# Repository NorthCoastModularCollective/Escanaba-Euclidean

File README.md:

# EuclideanTrigger
A simple module, based on the ATtiny85 that creates euclidean beats from a clock input. [under development]

The Escanaba Euclidean module has 3 alternate firmware modes:
## Escanaba Euclidean Firmware 
The Eucliean firmware generates euclidean rhythms synchronized to an external eurorack clock source. If no clock source is available it will self clock. Its 3 controls are as follows: 
- Number of hits
- Length of pattern in beats
- Pattern rotation. 
When in self clocking mode, the rotation control becomes a tempo control. 
## Calumet Clock Firmware
The Calument Clock firmware turns the module into a eurorack clock source. Its 3 controls are as follows:
- Swing control
- Clock Division/Multiplication
- Tempo
## Burst Generator
The Burst Generator firmware allows the module to respond to incoming trigger signals by repeating them in a variety of ways. This allows the creation of "bouncing ball" rhythms, ratchets, and other rhythmic tricks. Its controls are as follows:
- Number of repeats
- Initial repeat speed
- A "gravity" control that controls whether the repeats accelerate or decelerate in speed.

# Build instructions

[How to build the hardware](https://github.com/NorthCoastModularCollective/Escanaba-Euclidean/wiki/Build-Instructions)

# How To Setup Firmware

1. In the Arduino editor, in the tools menu, set the board to "AtTiny25/45/85"
2. In the Arduino editor, go to Sketch->Include Library->add .zip library and then select the lib folder from the project root.
3. set Processor to "AtTiny85"
4. set Clock to "Internal 16Mhz"
6. plug your programmer into a usb port. We reccomend the (TinyAvr programmer)[https://www.sparkfun.com/products/11801] from sparkfun
7. select your programmer in the tools menu (USBTinyISP if using the TinyAvr programmer - Note: Windows needs a driver for this to work)
8. in tools, select burn bootloader. Your AtTiny is now configured to run at 16Mhz.
9. now hit the upload button in the arduino editor to flash the firmware. (Note: if you're on a Mac, select "Sketch > Upload Using Programmer" because the upload button may throw an error about no programmer being available)
10. place the chip into the mount on the back of the module. Take care to make sure the dot on the back of the chip aligns with the indent on the PCB board diagram.
11. plug the module into your rack and have fun!

# License
All works are [CC BY NC](https://creativecommons.org/licenses/by-nc/4.0/) unless otherwise specified.

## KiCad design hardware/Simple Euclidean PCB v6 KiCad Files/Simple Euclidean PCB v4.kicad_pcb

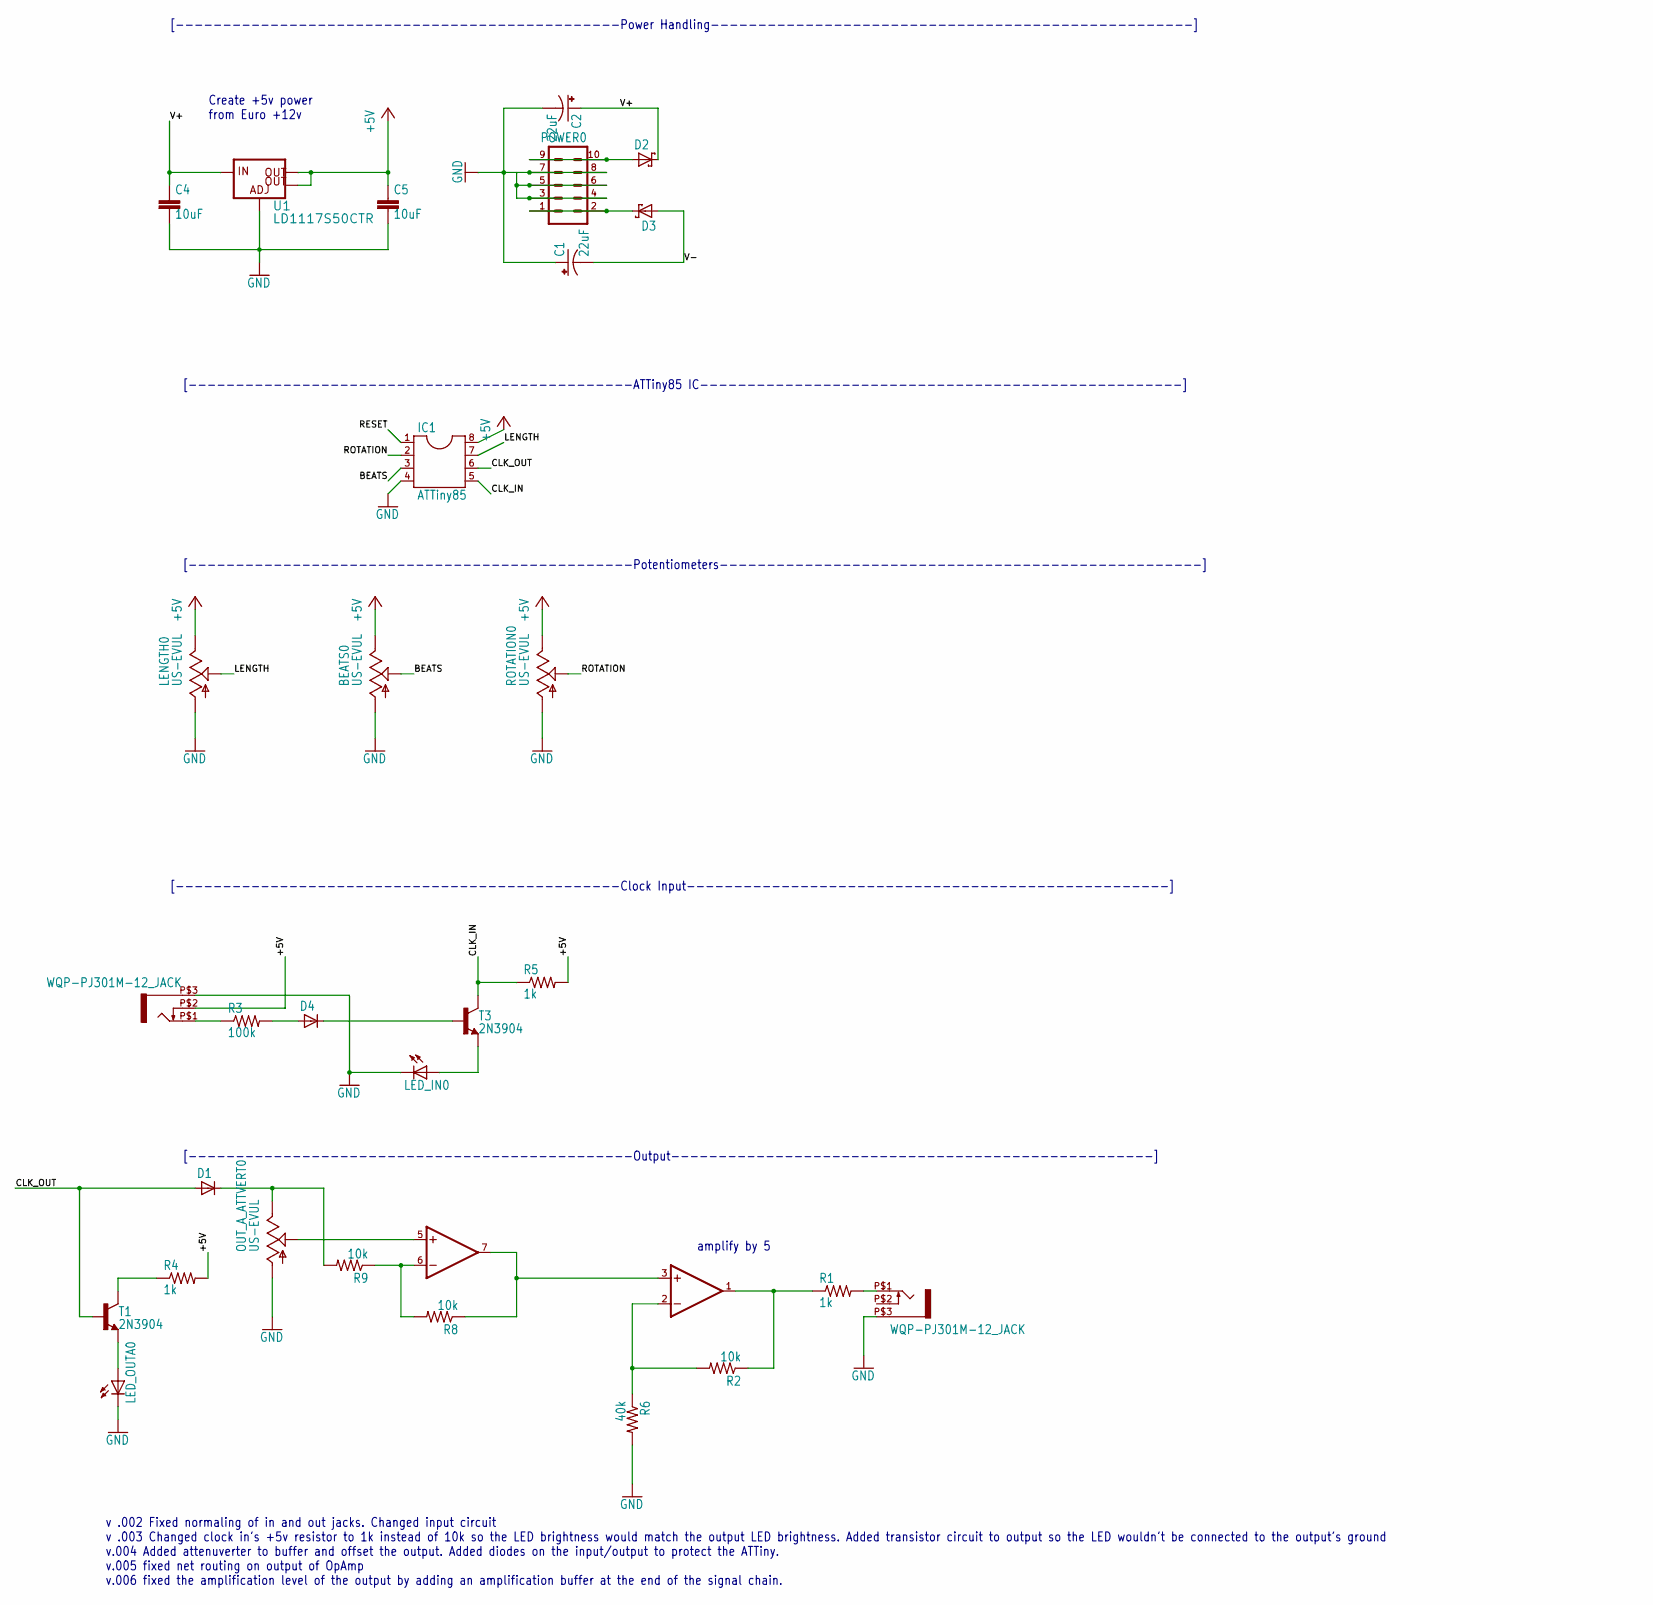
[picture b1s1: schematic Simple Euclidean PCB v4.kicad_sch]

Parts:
BEATS0: US-EVUL; EVUFXL
C1, C2: 22uF; E2,5-5
C4, C5: 10uF; C5B2.5
CLK_IN0: WQP-PJ301M-12_JACK
D1, D4: SMALL_DIODEDO35-7; DO35-7
D2, D3: SCHOTTKY-DIODEDO41; DO41-10
IC1: ATTiny85; DIL08
LED_IN0: LED3MM
LED_OUTA0: LED3MM
LENGTH0: US-EVUL; EVUFXL
OUT_A0: WQP-PJ301M-12_JACK
OUT_A_ATTVERT0: US-EVUL; EVUFXL
POWER0: MA05-2
R1, R4, R5: 1k; 0204_7
R2, R8, R9: 10k; 0204_7
R3: 100k; 0204_7
R6: 40k; 0204_7
ROTATION0: US-EVUL; EVUFXL
T1, T3: 2N3904; TO92
U1: LD1117S50CTR; SOT223
U2: TL072; DIL08-SML

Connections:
+5V: BEATS0.3 (E), C5.1, CLK_IN0.P$2 (3), IC1.8, LENGTH0.3 (E), R4.2, R5.2, ROTATION0.3 (E), U1.2 (OUT), U1.4 (OUT@1)
BEATS: BEATS0.2 (S), IC1.3
CLK_IN: IC1.5, R5.1, T3.1 (C)
CLK_IN1: R4.1, T1.1 (C)
CLK_OUT: D1.A, IC1.6, T1.2 (B)
GND: BEATS0.1 (A), C1.+, C2.-, C4.2, C5.2, CLK_IN0.P$3 (1), IC1.4, LED_IN0.K (C), LED_OUTA0.K (C), LENGTH0.1 (A), OUT_A0.P$3 (1), OUT_A_ATTVERT0.1 (A), POWER0.3, POWER0.4, POWER0.5, POWER0.6, POWER0.7, POWER0.8, R6.2, ROTATION0.1 (A), U1.1 (ADJ)
LENGTH: IC1.7, LENGTH0.2 (S)
unnamed: CLK_IN0.P$1 (2), R3.1
unnamed: OUT_A0.P$1 (2), R1.2
unnamed: D1.C, OUT_A_ATTVERT0.3 (E), R9.2
unnamed: D4.C, T3.2 (B)
unnamed: D4.A, R3.2
unnamed: LED_IN0.A, T3.3 (E)
unnamed: LED_OUTA0.A, T1.3 (E)
unnamed: R1.1, R2.1, U2.1 (OUT)
unnamed: R2.2, R6.1, U2.2 (-IN)
unnamed: OUT_A_ATTVERT0.2 (S), U2.5 (+IN)
unnamed: R8.2, R9.1, U2.6 (-IN)
unnamed: D2.A, POWER0.9, POWER0.10
unnamed: D3.C, POWER0.1, POWER0.2
OPAMPOUT: R8.1, U2.3 (+IN), U2.7 (OUT)
RESET: IC1.1
ROTATION: IC1.2, ROTATION0.2 (S)
V+: C2.+, C4.1, D2.C, U1.3 (IN), U2.8 (V+)
V-: C1.-, D3.A, U2.4 (V-)

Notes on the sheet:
amplify by 5
v .002 Fixed normaling of in and out jacks. Changed input circuit v .003 Changed clock in's +5v resistor to 1k instead of 10k so the LED brightness would match the output LED brightness. Added transistor circuit to output so the LED wouldn't be connected to the output's ground v.004 Added attenuver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
[-----------------------------------------------ATTiny85 IC---------------------------------------------------]
Create +5v power from Euro +12v
[-----------------------------------------------Clock Input---------------------------------------------------]
[-----------------------------------------------Power Handling---------------------------------------------------]
[-----------------------------------------------Output---------------------------------------------------]
[-----------------------------------------------Potentiometers---------------------------------------------------]

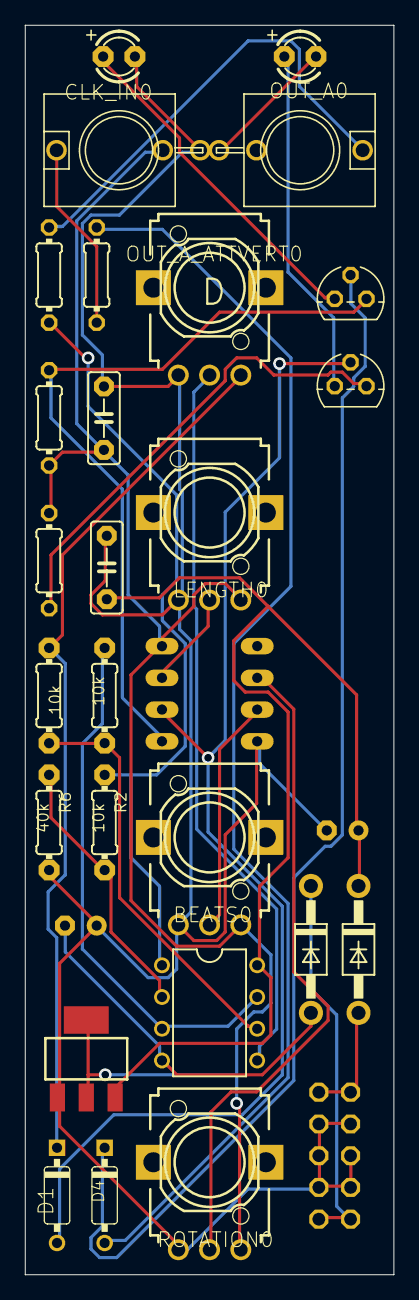
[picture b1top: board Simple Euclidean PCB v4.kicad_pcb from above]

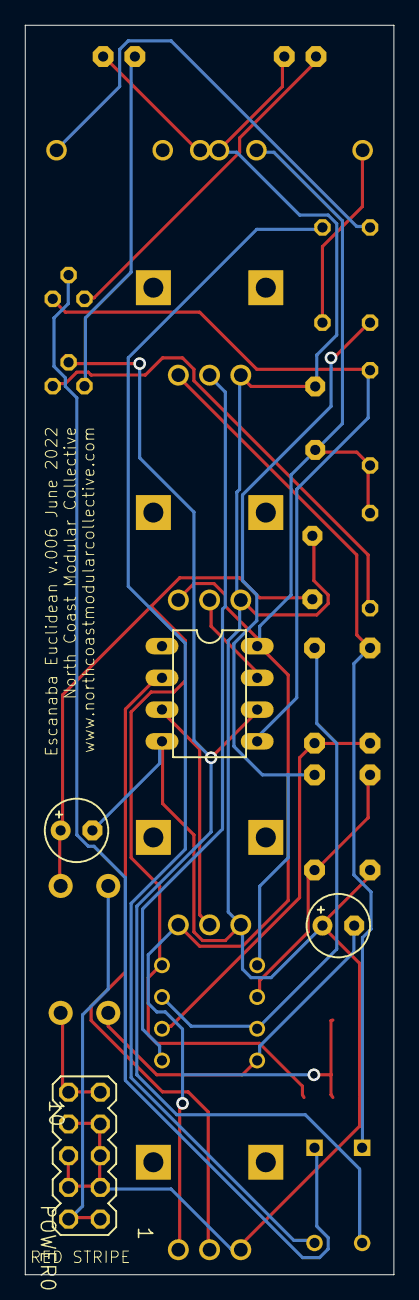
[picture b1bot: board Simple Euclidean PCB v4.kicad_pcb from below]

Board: 2 copper layers, 29.5 x 100.0 mm, 30 parts (4 on the bottom side), 24 nets.

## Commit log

2020-06-20 First version - hello world with an LED
2020-06-20 attempting to add debouncing to clock read
2020-06-28 Updated button schematic. Added IF logic.
    In this version, the test LED goes on once but only once. Should keep going on every time the button is pressed.
2020-07-05 Euclidean logic added
2020-08-25 Implemented internal clock mode. refactored code into pure functional core and imperitive shell.
2020-08-29 tempo knob behaves differently in the lower and upper segments of its range than in the middle, allowing for a greater range of musical tempos to be accessed in self clocking mode. also pulled out al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
2020-08-29 removing old versions of the ino...they will still be in history
2020-08-29 it appears i was overzealous... it still needs to be in a sketch folder for arduino ide
2020-09-13 oops... i had moved the set for previous trigger input state to earlier in the loop and it broke external clock mode... here is the fix
2021-07-01 comments made after session with Bill and Joe to review code
2021-07-02 did renames Bill suggested, then experimented with adding modifiers and introducing subroutines to clean up runloop.
2021-07-02 experiementing with hardware interrupt for reducing jitter in pulse output
2021-07-02 cleaning upISR implementation... not tested
2021-07-02 timer interrupt was wrong... making it turn on once as a debugging step
2021-07-03 playing with interrupt subdivision... need to run more tests
2021-07-03 removing interrupt code to get back to known working state... further interrupt experiments will happen on a branch
2021-07-03 known working version
2021-07-03 renames... tested working state
2021-07-03 added const modifier to pure functions
2021-07-03 rotation and beats knob range now depends on barlength
2021-07-03 adding instructions to run the module at 8Mhz as this speed fixes timing issues for now
2021-07-03 clock mode switch is more clearly labled
2021-07-03 first spike for clock firmware
2021-07-04 clock swing feature spike - tempo mult knob is working
2021-07-11 clock firmware now has rudimentary swing control
2021-07-30 external clock mode is broken... internal clock has basic functionality
2021-07-30 first version of the burst generator now works... external clock mode disabled
2021-07-30 clock firmware swing now has a deadspot in the middle of the knob range to ensure that 0 swing is accessible
2022-06-26 added schematic
2022-06-26 found a better way to share code among the 3 firmwares
2022-10-13 Update README.md
    Adding a bit more context to the readme to describe the function of alternate firmwares
2023-06-08 Update README.md
    added some details for Mac OS and Windows OS specific firmware setups
2023-06-27 Added panel designs
    Added PDFs of panel designs for the first time. These need to be updated and standardized (updating all 3 panels to the new width, etc), but they have the correct labels for controls.
2023-06-27 Added V12 of the Euclidean Panel
    Added V12 of the Euclidean Panel, and exported 3 separate layers for panel creation in KiCad.
2023-06-27 Added SVG version of panel exports
    Added SVG version of panel exports
2023-06-27 Removed old SVG, added new
2023-06-27 Create euclidean panel v12 DrillHoles v3.svg
    updated with only one layer
2023-06-27 One more try on the SVG file export for panels
2023-06-27 Create Asset 1.svg
    exported selection as assets instead of artboard
2023-06-27 test of Illustrator export
2023-06-28 Added new exports of layers as BMP
2023-06-28 Added TopoLines, updated PanelGraphics and overall panel design
2023-06-28 outlined text in Illustrator before export
2023-06-28 Tried export as DXF 2000
2023-06-28 Tried 1-bit BMP export
2023-06-28 Updated In/Our
2023-06-28 Added folders for each of the module variations
    Added folders for each of the module variations, reorganized files to make each version have its own discrete folder.
2023-06-28 added gerbers
2023-06-28 Updated schematics and gerbers
2023-06-29 Added SMD and Diodes images.
2023-06-29 Ceramic caps img
2023-06-29 socket and cap img
2023-06-29 transistor img
2023-06-29 power header img
2023-06-29 Knobs and pots img
2023-06-29 added KiCad fiels
2023-06-29 Update README.md
    added link to build instructions and added license
2023-06-30 Added topo lines to Belle Isle and Calumet panels
2023-06-30 Updated topo lines, exported as DXF for import to KiCad
    Updated topo lines, exported as DXF for import to KiCad
